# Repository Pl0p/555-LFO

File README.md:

# 555-LFO

## A small circuit for bend circuit and make some NOISE NOISE NOISE !

Should look like this :

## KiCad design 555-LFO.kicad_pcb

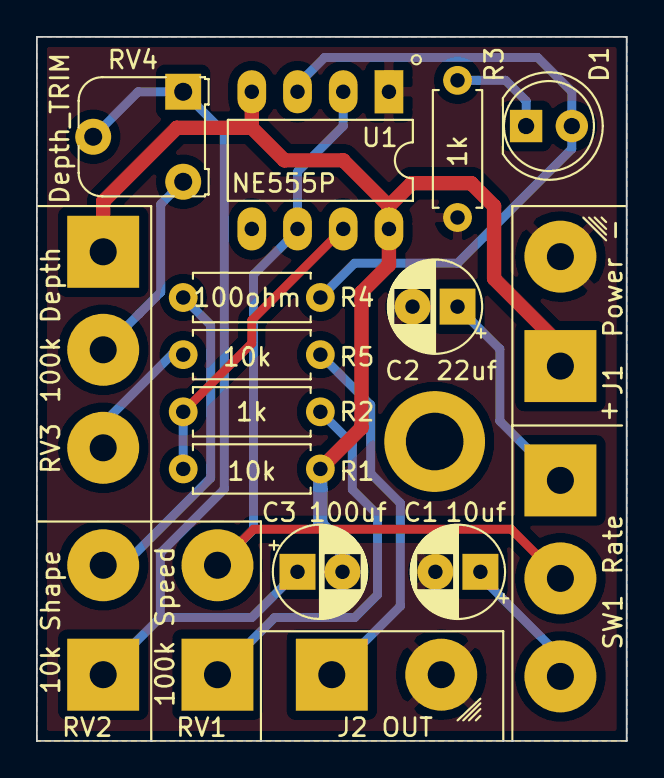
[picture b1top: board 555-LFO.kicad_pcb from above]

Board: 2 copper layers, 32.8 x 39.1 mm, 17 parts (0 on the bottom side), 14 nets.

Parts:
C1: 10uf; CP_Radial_5*11
C2: 22uf; CP_Radial_5*11
C3: 100uf; CP_Radial_5*11
D1: LED; LED_D5.0mm
J1: Power; Wire_Pad_1x02_Drill-1.5mm
J2: OUT; Wire_Pad_1x02_Drill-1.5mm
R1, R5: 10k; R_Axial_DIN0207_L6.3mm_D2.5mm_P7.62mm_Horizontal
R2, R3: 1k; R_Axial_DIN0207_L6.3mm_D2.5mm_P7.62mm_Horizontal
R4: 100; R_Axial_DIN0207_L6.3mm_D2.5mm_P7.62mm_Horizontal
RV1: 100k Speed; Wire_Pad_1x02_Drill-1.5mm
RV2: 10k Shape; Wire_Pad_1x02_Drill-1.5mm
RV3: 100k Depth; Wire_Pad_1x03_Drill-1.5mm
RV4: Depth_TRIM; Trimot_RM-065
SW1: Rate; Wire_Pad_1x03_Drill-1.5mm
U1: NE555P; DIP-8_Socket

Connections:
+9V: C3.2, J1.1, R1.2, RV3.1, U1.4, U1.8
GND: C1.2, C2.2, J1.2, J2.2, R3.2, U1.1
unnamed: C1.1, SW1.3
unnamed: C2.1, SW1.1
unnamed: C3.1, RV2.1, RV4.1, RV4.2
unnamed: D1.1, R3.1
unnamed: D1.2, R4.2, U1.3
unnamed: J2.1, R5.1
unnamed: R1.1, R2.2, U1.7
unnamed: R2.1, RV1.1
unnamed: R4.1, RV2.2
unnamed: R5.2, RV3.3
unnamed: RV1.2, SW1.2, U1.2, U1.6
unnamed: RV3.2, RV4.3

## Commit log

2021-08-07 555 LFO
